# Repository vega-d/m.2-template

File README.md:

# m.2-template
 this is a kicad project for a super simple m.2 ffpg B-key card that exposes usb 2.0 lanes

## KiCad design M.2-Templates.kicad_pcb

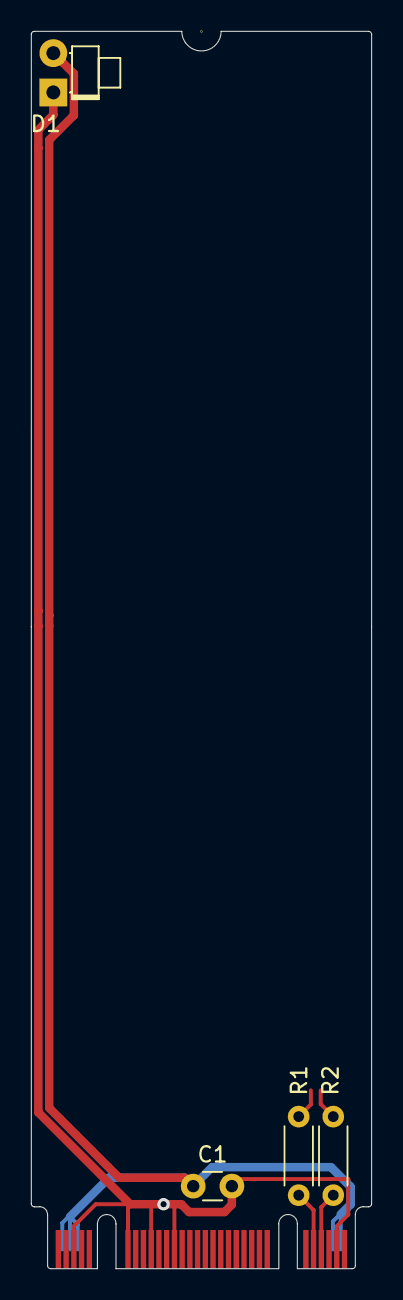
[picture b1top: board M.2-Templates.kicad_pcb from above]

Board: 2 copper layers, 22.0 x 80.0 mm, 5 parts (0 on the bottom side), 4 nets.

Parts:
C1: C_Small; C_Disc_D3.0mm_W1.6mm_P2.50mm
D1: LED; LED_D1.8mm_W1.8mm_H2.4mm_Horizontal_O1.27mm_Z1.6mm
R1, R2: R_Small; R_Axial_DIN0204_L3.6mm_D1.6mm_P5.08mm_Horizontal
U$1: M.2-B+M-KEY

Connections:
+3V3: C1.1, D1.2, U$1.P$2, U$1.P$4, U$1.P$70, U$1.P$72, U$1.P$74
GND: C1.2, D1.1, U$1.P$3, U$1.P$45, U$1.P$51, U$1.P$57, U$1.P$71
unnamed: R1.2, U$1.P$9
unnamed: R2.2, U$1.P$7
